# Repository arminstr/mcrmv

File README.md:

# mcrmv
/ˈmaɪˌkroʊ muv/

This is supposed to turn into a 100V 100A 10kW motor controller. Started designing the power section.

Work on [power stage](hardware/pwr/README.md) has started.

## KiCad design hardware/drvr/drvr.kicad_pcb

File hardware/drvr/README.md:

# drvr
/ˈdraɪvər/

### TL;DR
driver stage implementing solder pads for current tabs, shunt amplifiers, adc, parallel mosfet drivers, gate drive power supply, microcontroller for current and sensorless motor control

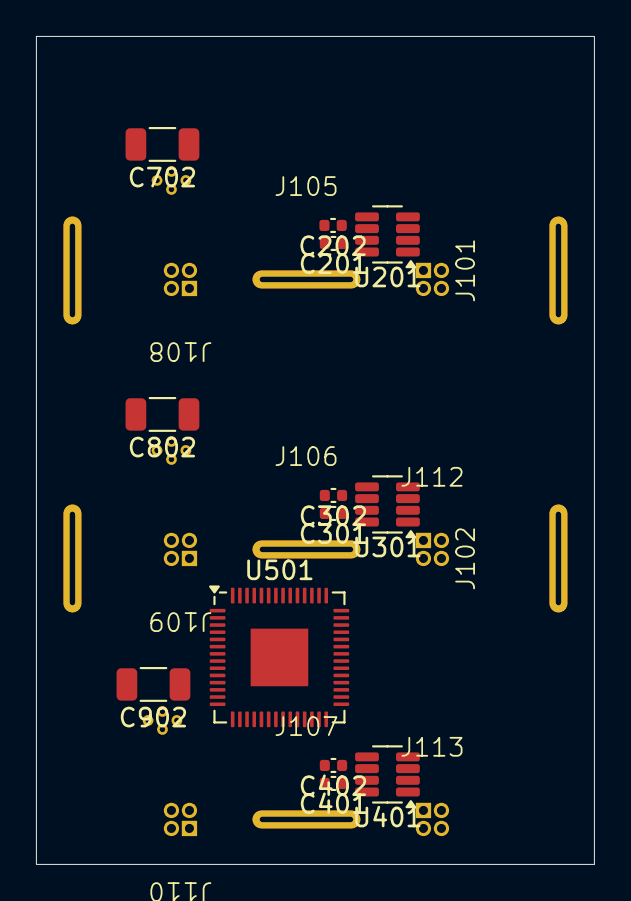
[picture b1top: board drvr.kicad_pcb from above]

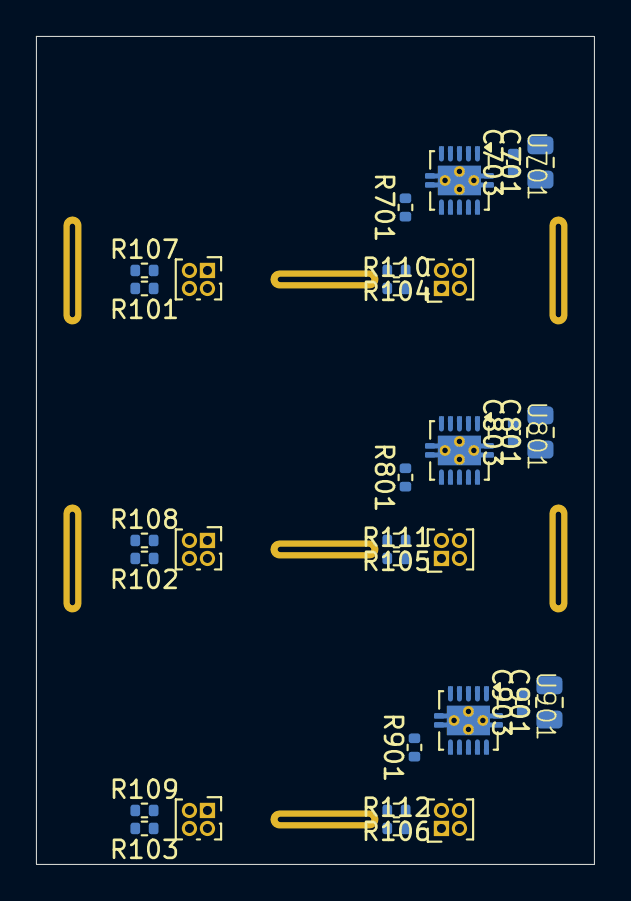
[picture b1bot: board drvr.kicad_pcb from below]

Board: 2 copper layers, 31.0 x 46.0 mm, 50 parts (24 on the bottom side), 39 nets, no tracks yet.

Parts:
C201, C202, C301, C302, C401, C402: 100nF; C_0402_1005Metric
C701, C801, C901: 2.2uF; C_0805_2012Metric
C702, C802, C902: 0.1uF; C_1206_3216Metric
C703, C803, C903: 0.1uF; C_0402_1005Metric
J101, J102, J103, J104, J105, J106, J107: pwrCon_Solder_5mm; 0.1x5mm_Strip_Cutout
J108, J109, J110, J111, J112, J113: PinHeader2x2; PinHeader2x2_1mm_Solder
R101, R102, R103, R104, R105, R106, R107, R108, R109, R110, R111, R112: 10; R_0402_1005Metric
R701, R801, R901: 10k; R_0402_1005Metric
U201, U301, U401: INA241A5xDDF; SOT-23-8
U501: RP2040; QFN-56-1EP_7x7mm_P0.4mm_EP3.2x3.2mm
U701, U801, U901: UCC27302A; DRC0010J-VSON-10

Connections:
+5V: C201.1, C301.1, C401.1, U201.7 (REF1), U301.7 (REF1), U401.7 (REF1)
+12V: C202.1, C302.1, C402.1, C701.2, C703.2, C801.2, C803.2, C901.2, C903.2, U201.6 (V+), U301.6 (V+), U401.6 (V+), U701.1 (VDD), U801.1 (VDD), U901.1 (VDD)
+80V: J101.1, J102.1
/GH_P1: R101.2, R107.1, U701.4 (HO)
/GH_P1_1: J111.2, R107.2
/GH_P1_2: J111.4, R101.1
/GH_P2: R102.2, R108.1, U801.4 (HO)
/GH_P2_1: J112.2, R108.2
/GH_P2_2: J112.4, R102.1
/GH_P3: R103.2, R109.1, U901.4 (HO)
/GH_P3_1: J113.2, R109.2
/GH_P3_2: J113.4, R103.1
/GL_P1: R104.2, R110.1, U701.10 (LO)
/GL_P1_1: J108.3, R104.1
/GL_P1_2: J108.1, R110.2
/GL_P2: R105.2, R111.1, U801.10 (LO)
/GL_P2_1: J109.3, R105.1
/GL_P2_2: J109.1, R111.2
/GL_P3: R106.2, R112.1, U901.10 (LO)
/GL_P3_1: J110.3, R106.1
/GL_P3_2: J110.1, R112.2
/P1: C702.1, J105.1, U701.5 (HS)
/P2: C802.1, J106.1, U801.5 (HS)
/P3: C902.1, J107.1, U901.5 (HS)
/S1_N: J111.3, U201.8 (+)
/S1_P: J111.1, U201.1 (-)
/S2_N: J112.3, U301.8 (+)
/S2_P: J112.1, U301.1 (-)
/S3_N: J113.3, U401.8 (+)
/S3_P: J113.1, U401.1 (-)
/gatedrive0/EN: R701.1, U701.6 (EN)
/gatedrive1/EN: R801.1, U801.6 (EN)
/gatedrive2/EN: R901.1, U901.6 (EN)
GND: C201.2, C202.2, C301.2, C302.2, C401.2, C402.2, C701.1, C703.1, C801.1, C803.1, C901.1, C903.1, J103.1, J104.1, J108.2, J109.2, J110.2, R701.2, R801.2, R901.2, U201.2 (GND), U201.3 (REF2), U201.4 (GND), U301.2 (GND), U301.3 (REF2), U301.4 (GND), U401.2 (GND), U401.3 (REF2), U401.4 (GND), U701.9 (VSS), U701.11 (EP), U801.9 (VSS), U801.11 (EP), U901.9 (VSS), U901.11 (EP)
unnamed: U501.23 (DVDD), U501.50 (DVDD)
unnamed: U501.1 (IOVDD), U501.10 (IOVDD), U501.22 (IOVDD), U501.33 (IOVDD), U501.42 (IOVDD), U501.49 (IOVDD)
unnamed: C702.2, U701.3 (HB)
unnamed: C802.2, U801.3 (HB)
unnamed: C902.2, U901.3 (HB)

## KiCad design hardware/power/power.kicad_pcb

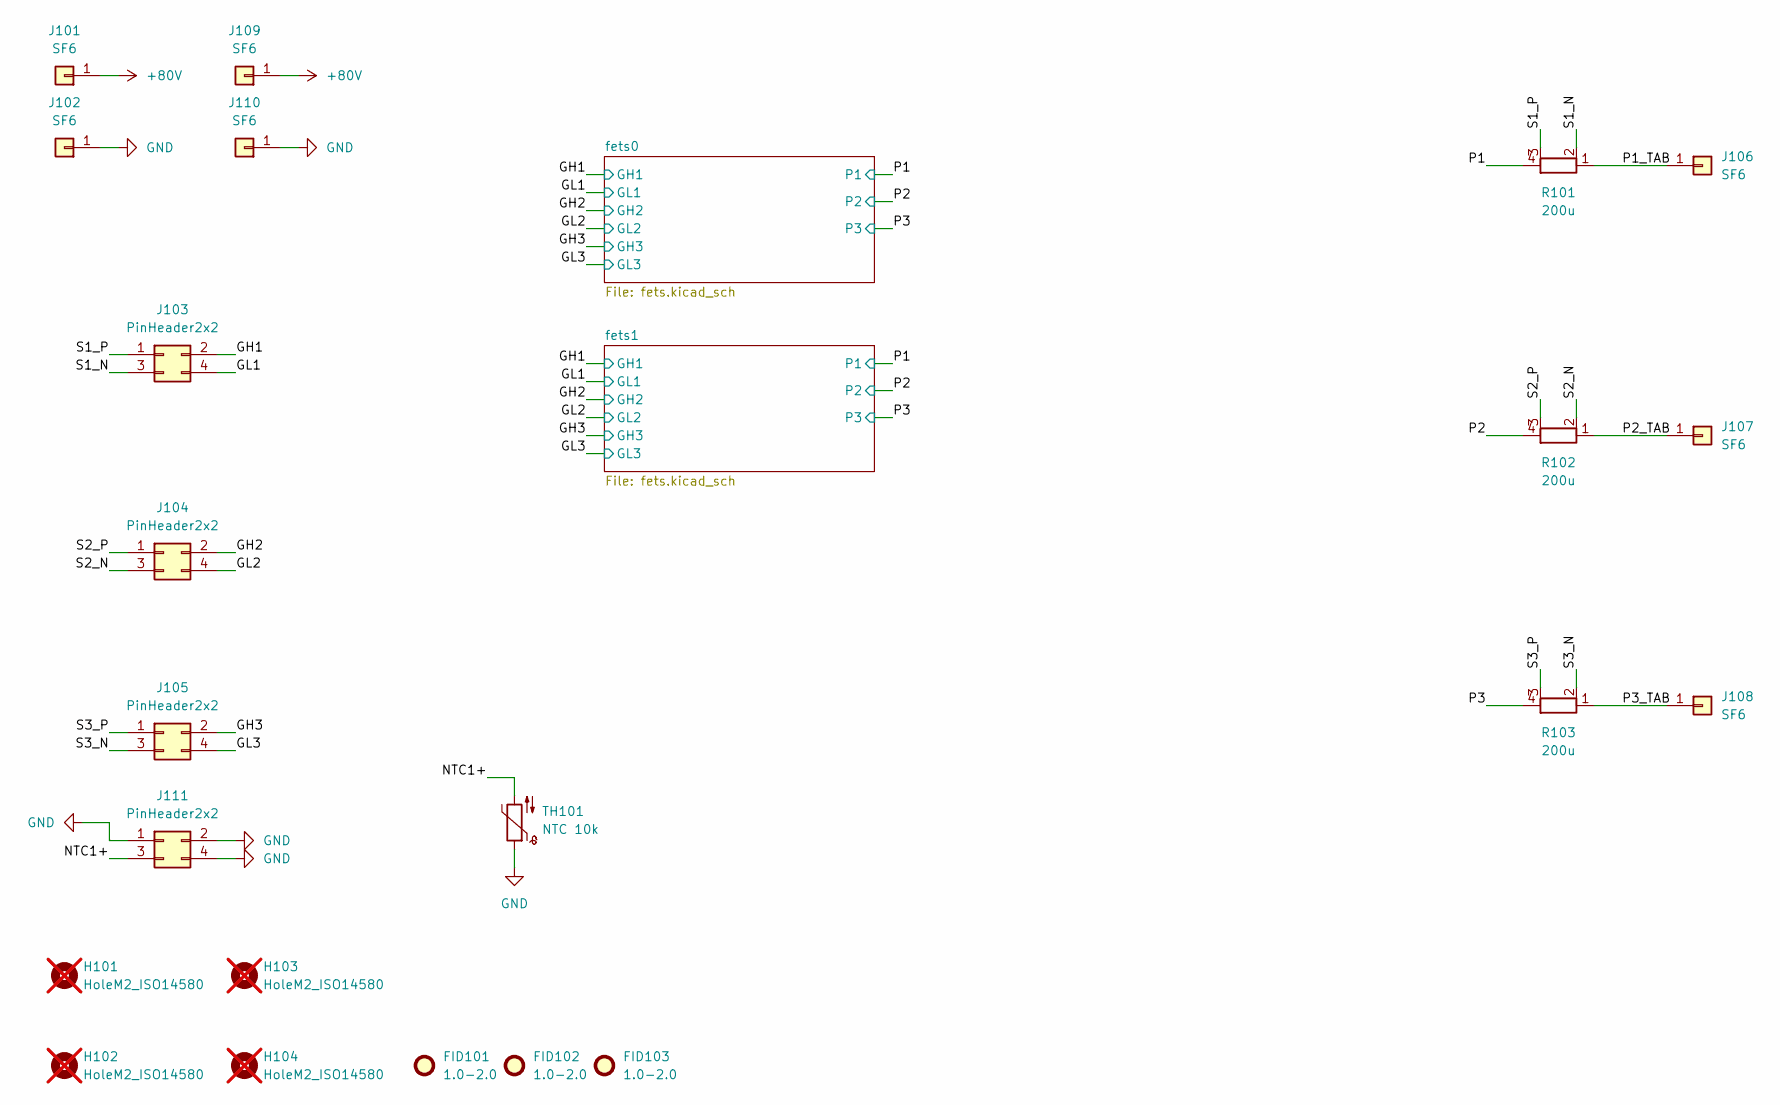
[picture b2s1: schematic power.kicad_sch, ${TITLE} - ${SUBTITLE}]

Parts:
FID101, FID102, FID103: 1.0-2.0; Fiducial_1mm_Mask2mm
H101, H102, H103, H104: HoleM2_ISO14580; MountingHole_2.2mm_M2_ISO14580; not fitted
J101, J102, J106, J107, J108, J109, J110: SF6; SolderWirePad_1x01_SMD_3x6mm
J103, J104, J105, J111: PinHeader2x2; PinHeader_2x02_P1.00mm_Vertical_SMD
R101, R102, R103: 200u; WSK1216; MPN WSK1216L2000FEA
TH101: NTC 10k; R_0402_1005Metric; MPN NTCG103JF103FT1

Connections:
+80V: J101.1, J109.1; also elsewhere on the board
/GH1: J103.2; also elsewhere on the board
/GH2: J104.2; also elsewhere on the board
/GH3: J105.2; also elsewhere on the board
/GL1: J103.4; also elsewhere on the board
/GL2: J104.4; also elsewhere on the board
/GL3: J105.4; also elsewhere on the board
/NTC1+: J111.3, TH101.2
/P1: R101.4; also elsewhere on the board
/P1_TAB: J106.1, R101.1
/P2: R102.4; also elsewhere on the board
/P2_TAB: J107.1, R102.1
/P3: R103.4; also elsewhere on the board
/P3_TAB: J108.1, R103.1
/S1_N: J103.3, R101.2
/S1_P: J103.1, R101.3
/S2_N: J104.3, R102.2
/S2_P: J104.1, R102.3
/S3_N: J105.3, R103.2
/S3_P: J105.1, R103.3
GND: J102.1, J110.1, J111.1, J111.2, J111.4, TH101.1; also elsewhere on the board

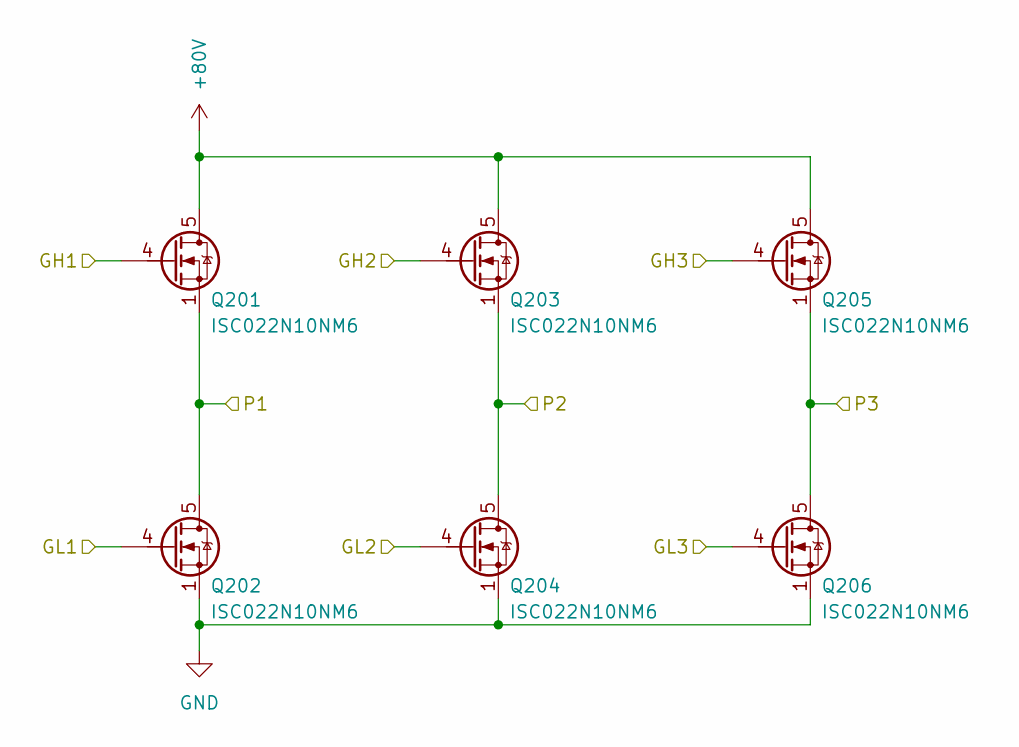
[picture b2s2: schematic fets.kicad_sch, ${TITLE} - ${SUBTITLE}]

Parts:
Q201, Q202, Q203, Q204, Q205, Q206: ISC022N10NM6; PowerPAK_SO-8_Single

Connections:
+80V: Q201.5 (D), Q203.5 (D), Q205.5 (D); also elsewhere on the board
/GH1: Q201.4 (G); also elsewhere on the board
/GH2: Q203.4 (G); also elsewhere on the board
/GH3: Q205.4 (G); also elsewhere on the board
/GL1: Q202.4 (G); also elsewhere on the board
/GL2: Q204.4 (G); also elsewhere on the board
/GL3: Q206.4 (G); also elsewhere on the board
/P1: Q201.1 (S), Q201.2 (S), Q201.3 (S), Q202.5 (D); also elsewhere on the board
/P2: Q203.1 (S), Q203.2 (S), Q203.3 (S), Q204.5 (D); also elsewhere on the board
/P3: Q205.1 (S), Q205.2 (S), Q205.3 (S), Q206.5 (D); also elsewhere on the board
GND: Q202.1 (S), Q202.2 (S), Q202.3 (S), Q204.1 (S), Q204.2 (S), Q204.3 (S), Q206.1 (S), Q206.2 (S), Q206.3 (S); also elsewhere on the board

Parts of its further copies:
Q301, Q302, Q303, Q304, Q305, Q306: ISC022N10NM6; PowerPAK_SO-8_Single

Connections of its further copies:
+80V: Q301.5 (D), Q303.5 (D), Q305.5 (D); also elsewhere on the board
/GH1: Q301.4 (G); also elsewhere on the board
/GH2: Q303.4 (G); also elsewhere on the board
/GH3: Q305.4 (G); also elsewhere on the board
/GL1: Q302.4 (G); also elsewhere on the board
/GL2: Q304.4 (G); also elsewhere on the board
/GL3: Q306.4 (G); also elsewhere on the board
/P1: Q301.1 (S), Q301.2 (S), Q301.3 (S), Q302.5 (D); also elsewhere on the board
/P2: Q303.1 (S), Q303.2 (S), Q303.3 (S), Q304.5 (D); also elsewhere on the board
/P3: Q305.1 (S), Q305.2 (S), Q305.3 (S), Q306.5 (D); also elsewhere on the board
GND: Q302.1 (S), Q302.2 (S), Q302.3 (S), Q304.1 (S), Q304.2 (S), Q304.3 (S), Q306.1 (S), Q306.2 (S), Q306.3 (S); also elsewhere on the board

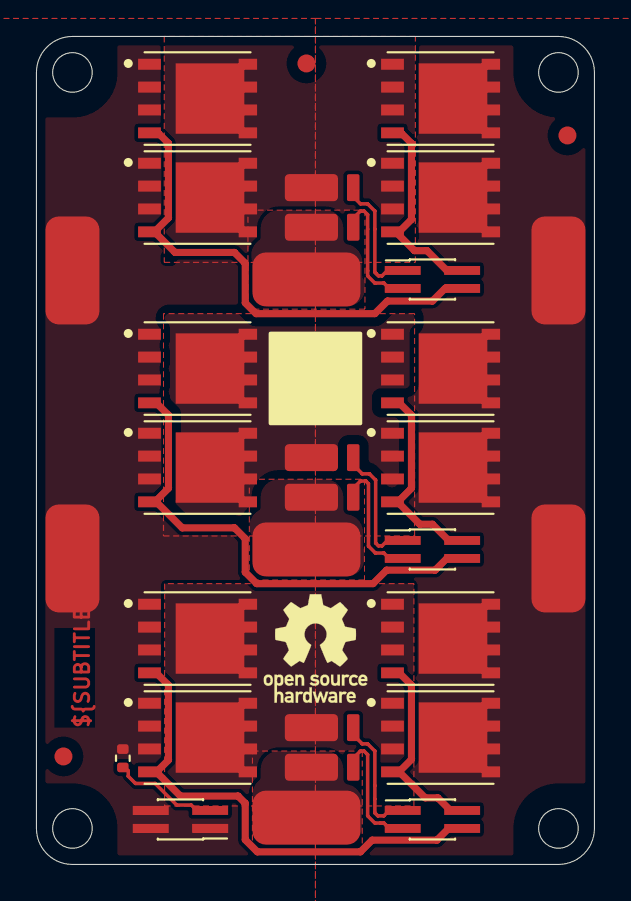
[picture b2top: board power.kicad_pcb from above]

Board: 2 copper layers, 31.0 x 46.0 mm, 34 parts (0 on the bottom side), 21 nets.

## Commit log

2025-10-23 initial commit including hardware board
2025-10-26 intermediate commit, some changes needed before first purchase
2025-10-26 added minimal info
2025-10-26 added connectors to add individual current paths, filled with ntcs, plotted pdf, updated screenshots
2025-10-26 renamed kicad project
2025-10-26 fixed link to power readme
2025-10-26 added NTC
2025-10-26 added empty project
2025-10-29 added current amps, basic PCB positions
2025-10-29 added solder targets, expanded project structure
2025-10-29 added initial description
2025-10-30 added initial gate-drive design
2025-10-30 added screenshot of intermediate design state to docs
2025-10-31 added gate driver footprint
2025-11-01 added gatedrivers + pico as draft
